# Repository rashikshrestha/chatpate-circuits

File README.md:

# chatpate-circuits
All Kicad files of chatpate project.

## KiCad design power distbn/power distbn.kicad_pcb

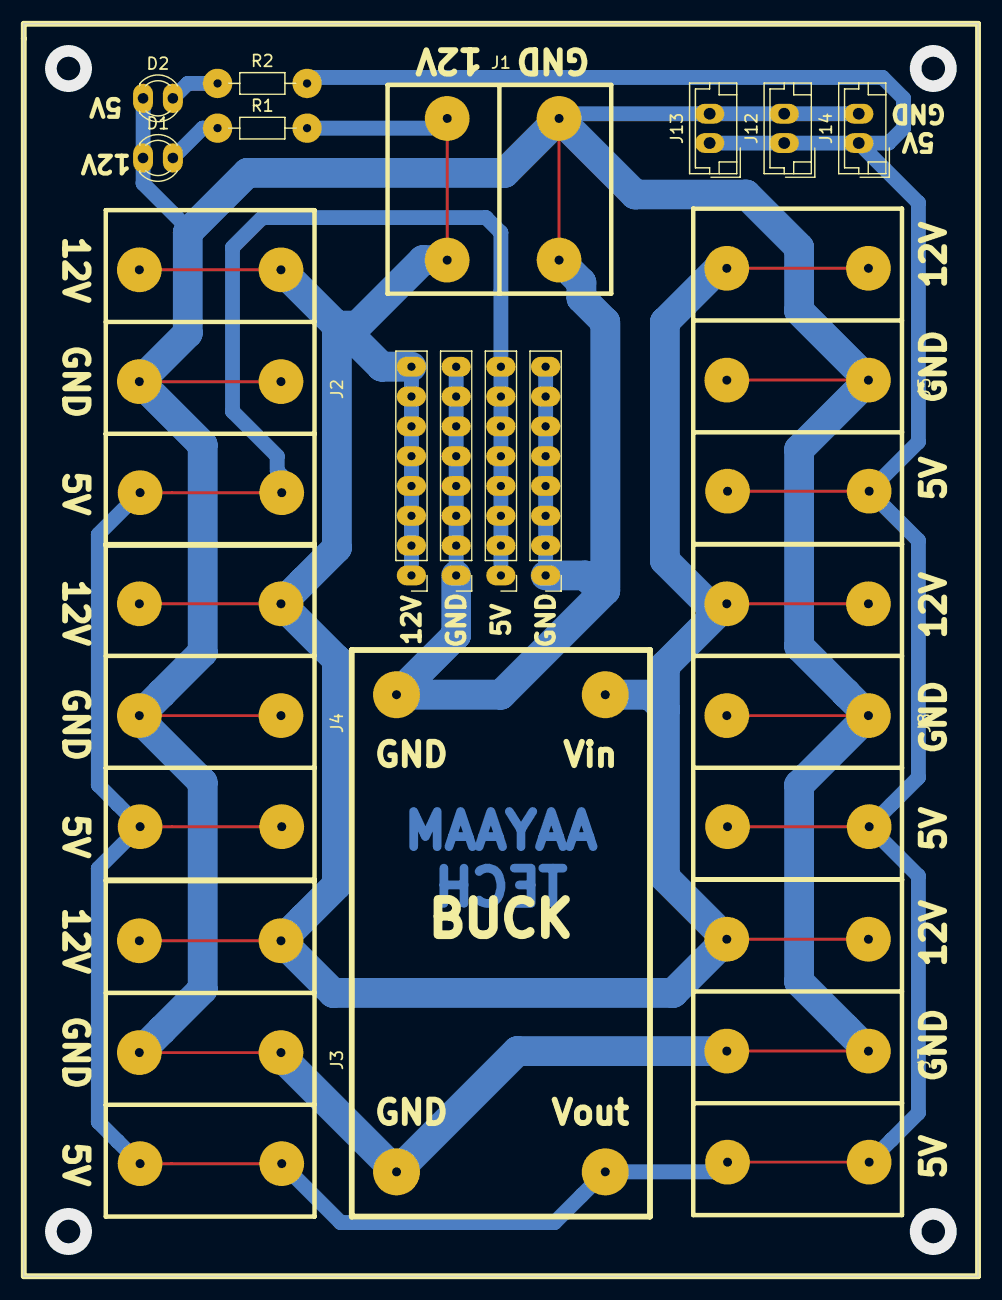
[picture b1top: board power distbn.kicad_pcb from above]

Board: 2 copper layers, 81.3 x 106.7 mm, 19 parts (0 on the bottom side), 5 nets.

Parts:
5V: 5V array; PinHeader_1x08_P2.54mm_Vertical
12V: 12V array; PinHeader_1x08_P2.54mm_Vertical
BUCK: BUCK; Buck
D1: 12V LED; LED_D3.0mm
D2: 5V LED; LED_D3.0mm
GND: GND array; PinHeader_1x08_P2.54mm_Vertical
GND#2: GND array; PinHeader_1x08_P2.54mm_Vertical
J1: POWER IN; Screw_Terminal_2_Pin
J2, J8: OUT 1; Screw_Terminal_3_Pin
J3: OUT 4; Screw_Terminal_3_Pin
J4: OUT 2; Screw_Terminal_3_Pin
J5: OUT 6; Screw_Terminal_3_Pin
J7: OUT 3; Screw_Terminal_3_Pin
J12, J13, J14: 5V OUT; JST_EH_B2B-EH-A_1x02_P2.50mm_Vertical
R1: 1K; R_Axial_DIN0204_L3.6mm_D1.6mm_P7.62mm_Horizontal
R2: 470; R_Axial_DIN0204_L3.6mm_D1.6mm_P7.62mm_Horizontal

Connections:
+5V: 5V.1, 5V.2, 5V.3, 5V.4, 5V.5, 5V.6, 5V.7, 5V.8, BUCK.4, J2.3, J3.3, J4.3, J5.3, J7.3, J8.3, J12.1, J13.1, J14.1, R2.2
+12V: 12V.1, 12V.2, 12V.3, 12V.4, 12V.5, 12V.6, 12V.7, 12V.8, BUCK.2, J1.1, J2.1, J3.1, J4.1, J5.1, J7.1, J8.1, R1.2
GND: BUCK.1, BUCK.3, D1.1, D2.1, GND.1, GND.2, GND.3, GND.4, GND.5, GND.6, GND.7, GND.8, GND#2.1, GND#2.2, GND#2.3, GND#2.4, GND#2.5, GND#2.6, GND#2.7, GND#2.8, J1.2, J2.2, J3.2, J4.2, J5.2, J7.2, J8.2, J12.2, J13.2, J14.2
unnamed: D1.2, R1.1
unnamed: D2.2, R2.1

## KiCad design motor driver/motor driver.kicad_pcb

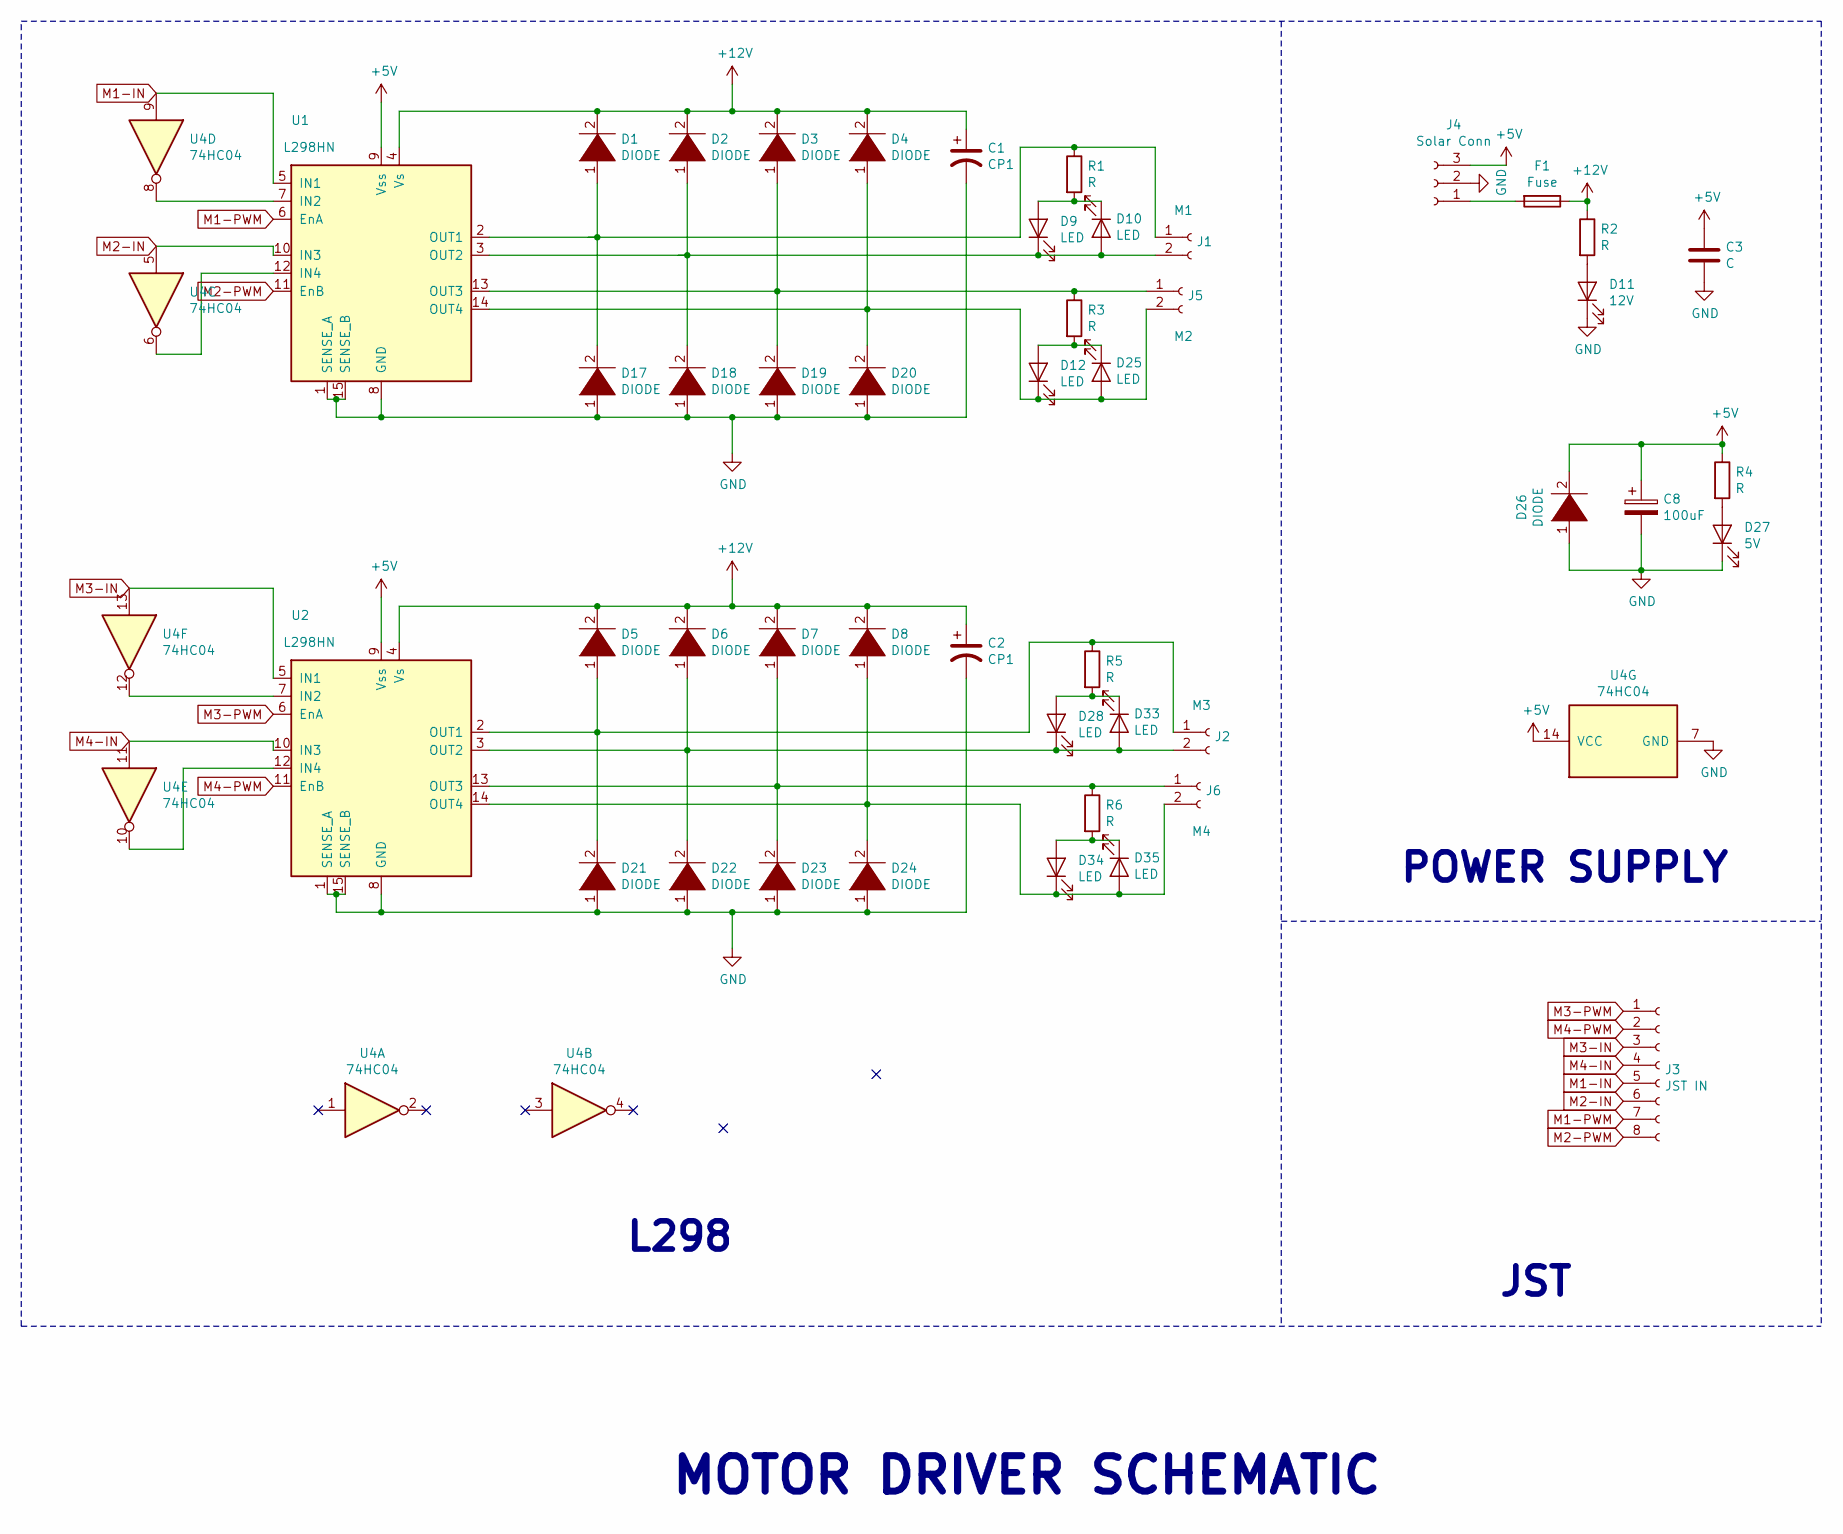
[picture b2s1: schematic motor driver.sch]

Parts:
C1, C2: CP1; CP_Radial_D5.0mm_P2.50mm
C3: C; C_Disc_D3.0mm_W2.0mm_P2.50mm
C8: 100uF; CP_Radial_D5.0mm_P2.50mm
D1, D2, D3, D4, D5, D6, D7, D8, D17, D18, D19, D20, D21, D22, D23, D24, D26: DIODE; D_A-405_P10.16mm_Horizontal
D9, D10, D12, D25, D28, D33, D34, D35: LED; LED_D3.0mm
D11: 12V; LED_D3.0mm
D27: 5V; LED_D3.0mm
F1: Fuse; fuse_holder
J1: M1; motor_connector
J2: M3; motor_connector
J3: JST IN; JST_EH_B8B-EH-A_1x08_P2.50mm_Vertical
J4: Solar Conn; Screw_Terminal_3_Pin
J5: M2; motor_connector
J6: M4; motor_connector
R1, R2, R3, R4, R5, R6: R; R_Axial_DIN0204_L3.6mm_D1.6mm_P7.62mm_Horizontal
U1, U2: L298HN; TO220-15
U4: 74HC04; DIP-14_W7.62mm_LongPads

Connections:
+5V: C3.1, C8.1, D26.2 (A), J4.3, R4.1, U1.9 (Vss), U2.9 (Vss), U4.14 (VCC)
+12V: C1.1, C2.1, D1.2 (A), D2.2 (A), D3.2 (A), D4.2 (A), D5.2 (A), D6.2 (A), D7.2 (A), D8.2 (A), F1.1, R2.1, U1.4 (Vs), U2.4 (Vs)
GND: C1.2, C2.2, C3.2, C8.2, D11.1 (K), D17.1 (K), D18.1 (K), D19.1 (K), D20.1 (K), D21.1 (K), D22.1 (K), D23.1 (K), D24.1 (K), D26.1 (K), D27.1 (K), J4.2, U1.1 (SENSE_A), U1.8 (GND), U1.15 (SENSE_B), U2.1 (SENSE_A), U2.8 (GND), U2.15 (SENSE_B), U4.7 (GND)
M1-IN: J3.5, U1.5 (IN1), U4.9
M1-PWM: J3.7, U1.6 (EnA)
M2-IN: J3.6, U1.10 (IN3), U4.5
M2-PWM: J3.8, U1.11 (EnB)
M3-IN: J3.3, U2.5 (IN1), U4.13
M3-PWM: J3.1, U2.6 (EnA)
M4-IN: J3.4, U2.10 (IN3), U4.11
M4-PWM: J3.2, U2.11 (EnB)
unnamed: D1.1 (K), D17.2 (A), J1.1, R1.1, U1.2 (OUT1)
unnamed: D9.2 (A), D10.1 (K), R1.2
unnamed: D2.1 (K), D9.1 (K), D10.2 (A), D18.2 (A), J1.2, U1.3 (OUT2)
unnamed: D11.2 (A), R2.2
unnamed: D4.1 (K), D12.1 (K), D20.2 (A), D25.2 (A), J5.2, U1.14 (OUT4)
unnamed: D12.2 (A), D25.1 (K), R3.2
unnamed: D3.1 (K), D19.2 (A), J5.1, R3.1, U1.13 (OUT3)
unnamed: D5.1 (K), D21.2 (A), J2.1, R5.1, U2.2 (OUT1)
unnamed: D6.1 (K), D22.2 (A), D28.1 (K), D33.2 (A), J2.2, U2.3 (OUT2)
unnamed: D7.1 (K), D23.2 (A), J6.1, R6.1, U2.13 (OUT3)
unnamed: D8.1 (K), D24.2 (A), D34.1 (K), D35.2 (A), J6.2, U2.14 (OUT4)
unnamed: D27.2 (A), R4.2
unnamed: D28.2 (A), D33.1 (K), R5.2
unnamed: D34.2 (A), D35.1 (K), R6.2
unnamed: F1.2, J4.1
unnamed: U1.7 (IN2), U4.8
unnamed: U1.12 (IN4), U4.6
unnamed: U2.7 (IN2), U4.12
unnamed: U2.12 (IN4), U4.10

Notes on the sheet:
MOTOR DRIVER SCHEMATIC
L298
POWER SUPPLY
JST

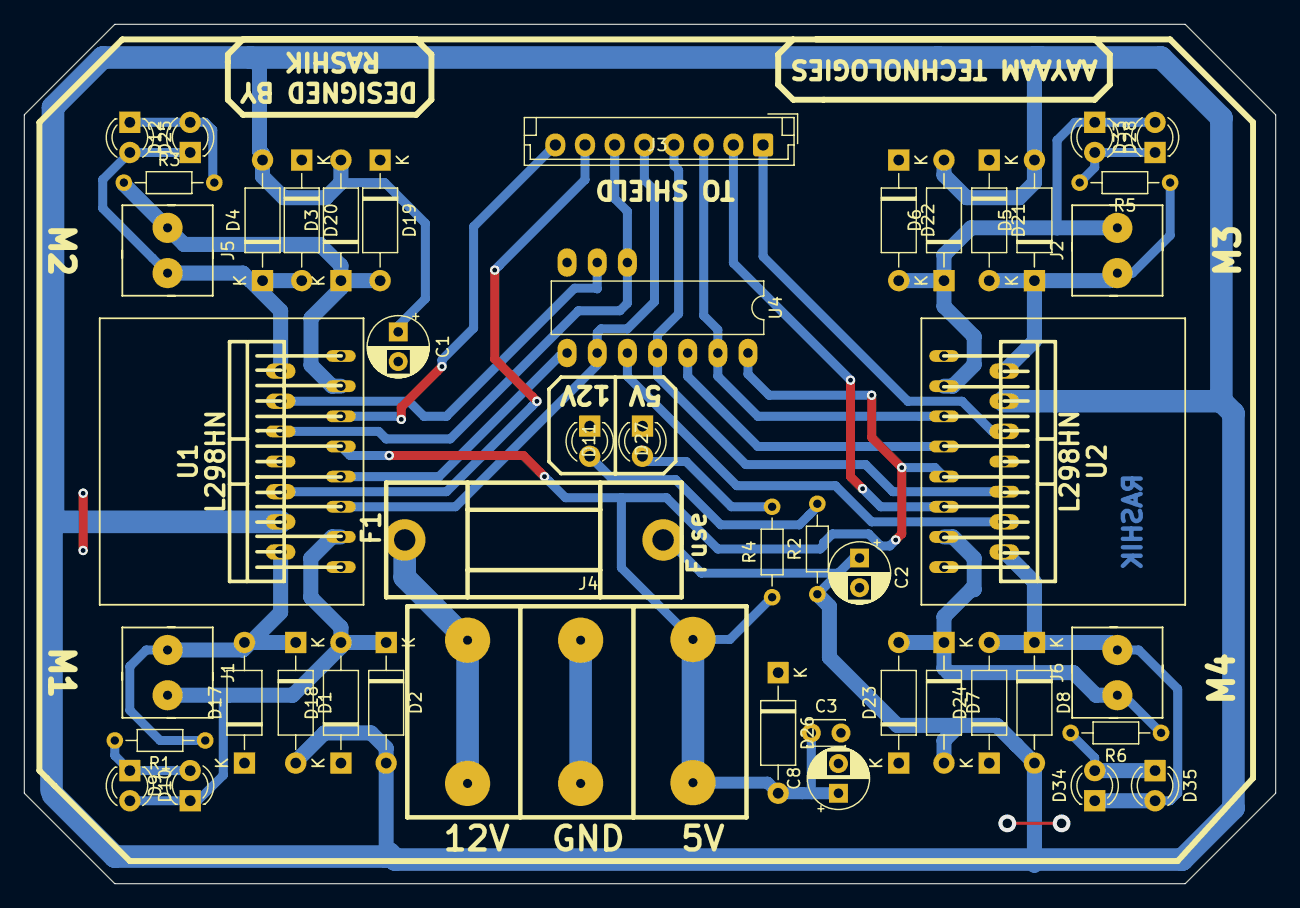
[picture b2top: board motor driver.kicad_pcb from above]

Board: 2 copper layers, 105.4 x 72.4 mm, 47 parts (0 on the bottom side), 30 nets.

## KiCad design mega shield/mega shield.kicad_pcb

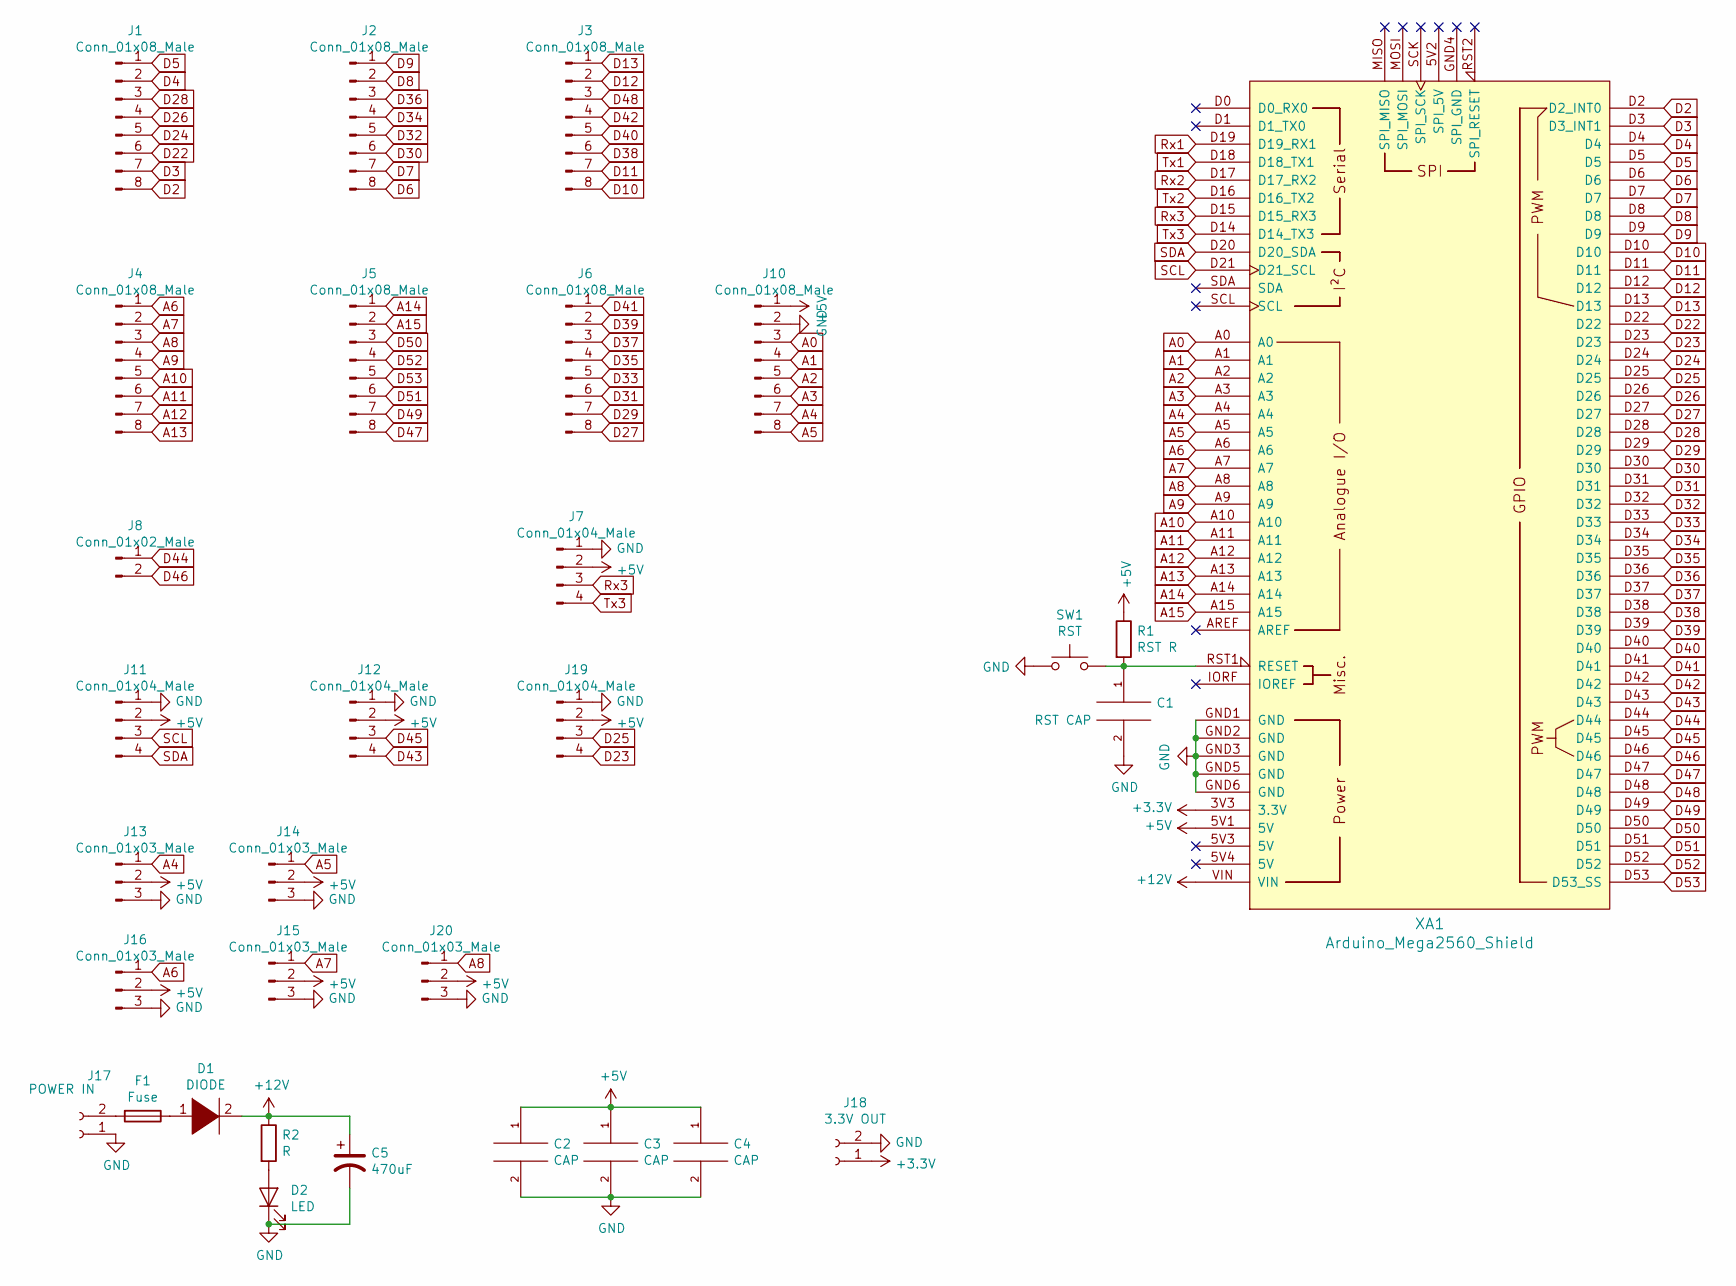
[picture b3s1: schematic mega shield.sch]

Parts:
C1: RST CAP; C_Disc_D3.4mm_W2.1mm_P2.50mm
C2, C3, C4: CAP; C_Disc_D3.4mm_W2.1mm_P2.50mm
C5: 470uF; CP_Radial_D8.0mm_P2.50mm
D1: DIODE; D_DO-27_P15.24mm_Horizontal
D2: LED; LED_D3.0mm
F1: Fuse; fuse_holder
J1, J2, J3, J4, J5, J6, J10: Conn_01x08_Male; JST_EH_B8B-EH-A_1x08_P2.50mm_Vertical
J7, J11, J12, J19: Conn_01x04_Male; JST_EH_B4B-EH-A_1x04_P2.50mm_Vertical
J8: Conn_01x02_Male; JST_EH_B2B-EH-A_1x02_P2.50mm_Vertical
J13, J14, J15, J16, J20: Conn_01x03_Male; JST_EH_B3B-EH-A_1x03_P2.50mm_Vertical
J17: POWER IN; Screw_Terminal_2_Pin
J18: 3.3V OUT; JST_EH_B2B-EH-A_1x02_P2.50mm_Vertical
R1: RST R; R_Axial_DIN0207_L6.3mm_D2.5mm_P7.62mm_Horizontal
R2: R; R_Axial_DIN0207_L6.3mm_D2.5mm_P7.62mm_Horizontal
SW1: RST; SW_PUSH_6mm_H5mm
XA1: Arduino_Mega2560_Shield

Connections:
+3V3: J18.1, XA1.3V3 (3.3V)
+5V: C2.1, C3.1, C4.1, J7.2, J10.1, J11.2, J12.2, J13.2, J14.2, J15.2, J16.2, J19.2, J20.2, R1.1, XA1.5V1 (5V)
+12V: C5.1, D1.2 (A), R2.1, XA1.VIN
A0: J10.3, XA1.A0
A1: J10.4, XA1.A1
A2: J10.5, XA1.A2
A3: J10.6, XA1.A3
A4: J10.7, J13.1, XA1.A4
A5: J10.8, J14.1, XA1.A5
A6: J4.1, J16.1, XA1.A6
A7: J4.2, J15.1, XA1.A7
A8: J4.3, J20.1, XA1.A8
A9: J4.4, XA1.A9
A10: J4.5, XA1.A10
A11: J4.6, XA1.A11
A12: J4.7, XA1.A12
A13: J4.8, XA1.A13
A14: J5.1, XA1.A14
A15: J5.2, XA1.A15
D2: J1.8, XA1.D2 (D2_INT0)
D3: J1.7, XA1.D3 (D3_INT1)
D4: J1.2, XA1.D4
D5: J1.1, XA1.D5
D6: J2.8, XA1.D6
D7: J2.7, XA1.D7
D8: J2.2, XA1.D8
D9: J2.1, XA1.D9
D10: J3.8, XA1.D10
D11: J3.7, XA1.D11
D12: J3.2, XA1.D12
D13: J3.1, XA1.D13
D22: J1.6, XA1.D22
D23: J19.4, XA1.D23
D24: J1.5, XA1.D24
D25: J19.3, XA1.D25
D26: J1.4, XA1.D26
D27: J6.8, XA1.D27
D28: J1.3, XA1.D28
D29: J6.7, XA1.D29
D30: J2.6, XA1.D30
D31: J6.6, XA1.D31
D32: J2.5, XA1.D32
D33: J6.5, XA1.D33
D34: J2.4, XA1.D34
D35: J6.4, XA1.D35
D36: J2.3, XA1.D36
D37: J6.3, XA1.D37
D38: J3.6, XA1.D38
D39: J6.2, XA1.D39
D40: J3.5, XA1.D40
D41: J6.1, XA1.D41
D42: J3.4, XA1.D42
D43: J12.4, XA1.D43
D44: J8.1, XA1.D44
D45: J12.3, XA1.D45
D46: J8.2, XA1.D46
D47: J5.8, XA1.D47
D48: J3.3, XA1.D48
D49: J5.7, XA1.D49
D50: J5.3, XA1.D50
D51: J5.6, XA1.D51
D52: J5.4, XA1.D52
D53: J5.5, XA1.D53 (D53_SS)
GND: C1.2, C2.2, C3.2, C4.2, C5.2, D2.1 (K), J7.1, J10.2, J11.1, J12.1, J13.3, J14.3, J15.3, J16.3, J17.1, J18.2, J19.1, J20.3, SW1.1, XA1.GND1 (GND), XA1.GND2 (GND), XA1.GND3 (GND), XA1.GND5 (GND), XA1.GND6 (GND)
unnamed: C1.1, R1.2, SW1.2, XA1.RST1 (RESET)
unnamed: D1.1 (K), F1.1
unnamed: D2.2 (A), R2.2
unnamed: F1.2, J17.2
Rx1: XA1.D19 (D19_RX1)
Rx2: XA1.D17 (D17_RX2)
Rx3: J7.3, XA1.D15 (D15_RX3)
SCL: J11.3, XA1.D21 (D21_SCL)
SDA: J11.4, XA1.D20 (D20_SDA)
Tx1: XA1.D18 (D18_TX1)
Tx2: XA1.D16 (D16_TX2)
Tx3: J7.4, XA1.D14 (D14_TX3)

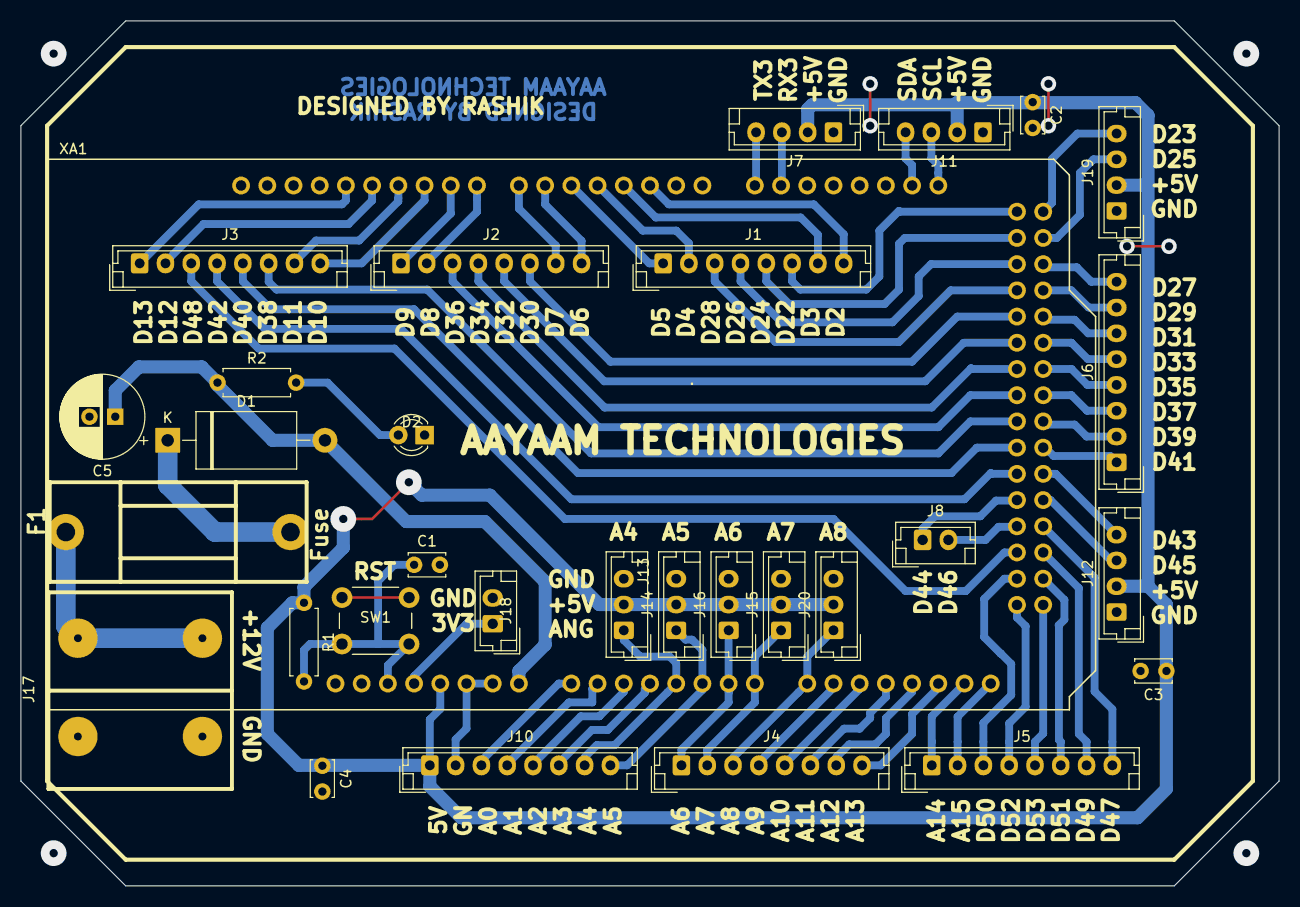
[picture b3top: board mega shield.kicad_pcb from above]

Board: 2 copper layers, 121.9 x 83.8 mm, 31 parts (0 on the bottom side), 72 nets.

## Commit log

2019-05-21 motor driver added
2019-05-21 just a commit
2019-05-22 mega shield sch done
2019-05-22 mega shield 80% done
2019-05-23 mega shield completed
2019-05-23 mega shield updated ali
2019-05-30 motor driver done
2019-07-15 Power distribution board added
2019-07-15 power distbn added
